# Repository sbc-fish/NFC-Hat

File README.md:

# NFC-Hat
A PN7150 NFC hat for SFPi and Raspberry Pi

Please refer to [linux_libnfc-nci](https://github.com/NXPNFCLinux/linux_libnfc-nci) for the firmware.

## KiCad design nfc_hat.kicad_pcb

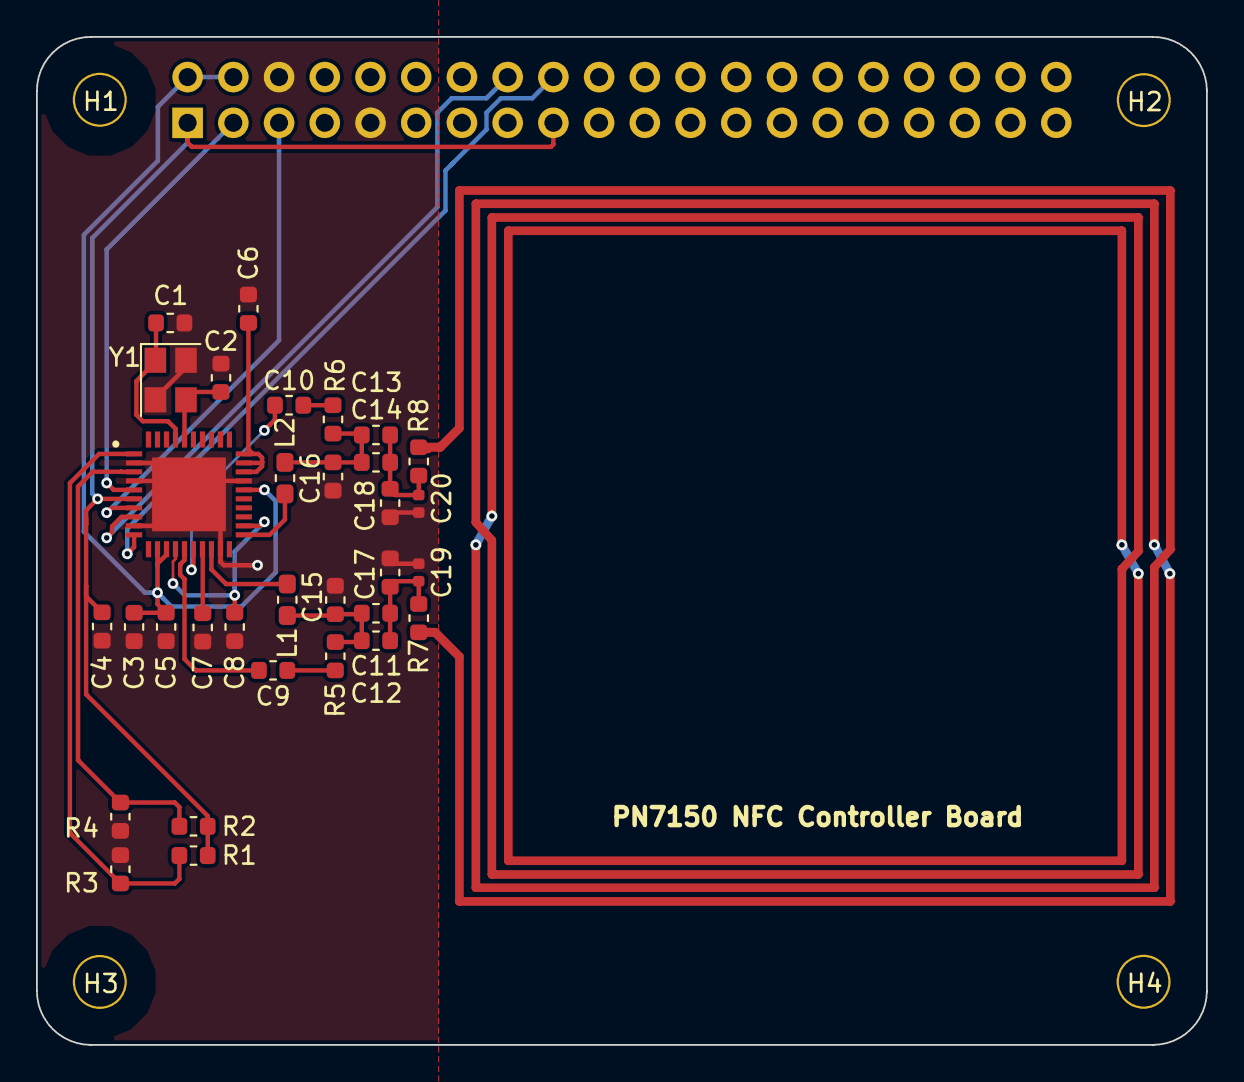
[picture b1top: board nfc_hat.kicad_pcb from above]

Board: 4 copper layers, 65.0 x 56.0 mm, 37 parts (1 on the bottom side), 25 nets.

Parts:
C1, C2: 10pF 50V; C_0603_1608Metric
C3: 4.7uF; C_0603_1608Metric
C4, C6: 1uF; C_0603_1608Metric
C5: 100nF; C_0603_1608Metric
C7: 100nF 50V; C_0603_1608Metric
C8: 1uF 50V; C_0603_1608Metric
C9, C10: 1nF; C_0603_1608Metric
C11, C14: 56pF; C_0603_1608Metric
C12, C13: 22pF; C_0603_1608Metric
C15, C16: 680pF; C_0603_1608Metric
C17, C18: 120pF; C_0603_1608Metric
C19, C20: 2.2pF; C_0402_1005Metric
H1, H2, H3, H4: 3mm_Mounting_Hole; NPTH_3mm_ID
J3: 40HAT; PinSocket_2x20_P2.54mm_Vertical
L1, L2: 160nH; L_0603_1608Metric_Pad1.05x0.95mm_HandSolder
R1, R2: NC; R_0603_1608Metric
R3, R4: 100K; R_0603_1608Metric
R5, R6: 2.2K; R_0603_1608Metric
R7, R8: 1.5; R_0603_1608Metric
U1: PN7150; HVQFN40-6x6
Y1: 27.12Mhz; Crystal_SMD_3225-4Pin_3.2x2.5mm

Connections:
GND: C1.2, C2.2, C3.2, C4.2, C5.2, C6.2, C7.2, C8.1, C15.1, C16.1, C17.1, C18.2, C19.1, C20.2, J3.6, J3.9, J3.14, J3.20, J3.25, J3.30, J3.34, J3.39, R3.1, R4.1, U1.2, U1.4, U1.9, U1.19, U1.27, U1.EXP, Y1.2, Y1.4
I2C_SCL: J3.5, U1.7
I2C_SDA: J3.3, U1.5
IRQ: J3.16, U1.8
unnamed: R7.2, R8.2
unnamed: C1.1, U1.37, Y1.1
unnamed: C2.1, U1.36, Y1.3
unnamed: C6.1, U1.28, U1.29, U1.30
unnamed: C7.1, U1.17
unnamed: C8.2, U1.14, U1.22
unnamed: C9.1, R5.1
unnamed: C9.2, U1.15
unnamed: C10.1, R6.1
unnamed: C10.2, U1.16
unnamed: C11.1, C12.1, C17.2, C19.2, R7.1
unnamed: C11.2, C12.2, C15.2, L1.2, R5.2
unnamed: C13.1, C14.1, C18.1, C20.1, R8.1
unnamed: C13.2, C14.2, C16.2, L2.2, R6.2
unnamed: L1.1, U1.18
unnamed: L2.1, U1.21
unnamed: R1.1, R3.2, U1.1
unnamed: R2.1, R4.2, U1.3
PVDD: C4.1, J3.1, J3.17, R1.2, R2.2, U1.6
VBAT: C3.1, C5.1, J3.2, J3.4, U1.12, U1.13, U1.26
VEN: J3.18, U1.10

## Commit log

2019-03-21 Add files
2019-10-19 Fix path in sym-lib-table
    Use variable instead of hard-coded path for local library
